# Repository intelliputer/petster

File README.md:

## The Petster Deluxe

An archival and reverse-engineering workspace for the Axlon Petster Deluxe electronic pet.

### What is preserved

Petster Deluxe is an electronic pet with a microprocessor-controlled behaviour system. It responds to sounds and touch, can be led by a leash, and uses forward sensing to avoid obstacles.

The central artifact is a 4 KiB ROM image. The 8039 is an Intel MCS-48-family controller with external program memory; the bundled 8048-family references and tools are included to support investigation of that ROM.

| Path | Purpose |
| --- | --- |
| [`code/petster.bin`](code/petster.bin) | Preserved 4,096-byte baseline ROM image. |
| [`code/petster.hex`](code/petster.hex) | Intel HEX encoding of the canonical ROM. |
| [`code/petster-array`](code/petster-array) | C-style byte-array representation. |
| [`code/PetsterDeluxeEprom.zip`](code/PetsterDeluxeEprom.zip) | Original-style archive containing the same ROM payload. |
| [`src/README.md`](src/README.md) | Read-only procedure for dumping the EPROM from the working Petster with the Barlino II. |
| [`src/petster_8039_linear.asm`](src/petster_8039_linear.asm) | Reproducible mechanical MCS-48/INS8039 assembly-style listing. |
| [`src/ROM-CONTROL-FLOW.md`](src/ROM-CONTROL-FLOW.md) | Tentative ROM control-flow map, with editable Mermaid source and SVG. |
| [`docs/`](docs) | Owner's manual, technical guide, and reference material. |
| [`docs/TECHNICAL-RESEARCH.md`](docs/TECHNICAL-RESEARCH.md) | Sourced 1985 hardware findings, preserved teardown, and open questions. |
| [`datasheets/`](datasheets) | INS8039-family reference datasheet. |
| [`docs/UNIT-OBSERVATIONS.md`](docs/UNIT-OBSERVATIONS.md) | Owner-reported markings and the evidence still needed from this specific cat. |
| [`tools/`](tools/README.md) | Period 8048/8039 development and analysis tools. |

### Hardware status

The 27C128 banked-ROM daughterboard is now a routed, two-layer PCB suitable
for a standard fabrication run. It adapts the Petster's 24-pin National
`NMC27C32` socket to a 28-pin `27C128`, with two jumpers selecting A12 and
A13 (four 4 KiB banks). Its functional pin assignments have been checked
against the NMC27C32B and 27C128 datasheets.

| Item | Current state |
| --- | --- |
| KiCad source | [`hardware/27c128-daughterboard/`](hardware/27c128-daughterboard/) |
| PCB | Routed, 45 × 45 mm, two copper layers, 0.20 mm tracks |
| Electrical rules check | 0 violations; 0 unconnected items in the prior KiCad check (2026-11-02); rerun before fabrication |
| Production archive | [`27c128-daughterboard.zip`](hardware/27c128-daughterboard/production/27c128-daughterboard.zip) |
| Latest fabrication export | Regenerated with KiCad 10.0.8 on 2026-11-03; J1 is now a 0.7 mm drilled 24-pin wide-DIP plug footprint |
| Solder mask | Present on both sides and on all plated pads |
| Hardware test | Pending continuity checks, then a controlled power-on test in the Petster |

This is a passive adapter: it relies on the Petster's existing +5 V supply
and external-ROM signals. Fit C1, both bank-select shunts, the 24-pin male
plug, and the 28-pin socket before use. Do not change bank jumpers while the
Petster is powered.

The companion 8039-II SBC is also released for fabrication. It is a two-layer
external-ROM MCS-48 bench computer with a socketed 8039, 74LS373 address latch,
27C32/27C128/27C256 ROM socket, FTDI Friend console, and a 20-pin expansion
header. Its 8039 multiplexed DB0-DB7 bus is connected to both the latch and
ROM; J2 instead exposes the spare P1/P2 GPIO and external-bus control signals.

| Item | Current state |
| --- | --- |
| KiCad source | [`hardware/8039-II-SBC/`](hardware/8039-II-SBC/) |
| PCB | Routed two-layer through-hole board; 0 unconnected pads |
| Design checks | ERC: 0 errors / 0 warnings; DRC: 0 violations (2026-11-05) |
| Production archive | [`8039-II-SBC.zip`](hardware/8039-II-SBC/production/8039-II-SBC.zip) |
| Electrical design | [`ELECTRICAL-ANALYSIS.md`](hardware/8039-II-SBC/ELECTRICAL-ANALYSIS.md) |
| Assembly status | Fabrication-ready; first assembled-board bring-up remains pending |

Use the [8039-II bring-up checklist](hardware/8039-II-SBC/BRING-UP.md) for
first power-up. Verify jumper positions and component orientation, then use a
current-limited 5 V source and a known-good diagnostic EPROM image.

### ROM integrity and physical provenance

The ZIP payload, Intel HEX file, `src` binary, and C-style byte array resolve
byte-for-byte to the preserved baseline image. The image is 4,096 bytes and
has this SHA-256 digest:

```text
609d6505297a6365abb4fdbd869a2d76aad65ebd2accc628e37023a11ffefee9
```

Run the following from the repository root to verify those representations:

```sh
./scripts/verify-rom.sh
```

The check requires standard POSIX utilities plus `unzip`, GNU `objcopy`, and `sha256sum`.

This proves that the repository copies agree; it does **not** prove the image
matches the ROM in any particular Petster Deluxe. The working Petster's EPROM
is the authority for that unit. Use the read-only
[`src/README.md`](src/README.md) procedure to make two independent Barlino II
reads, compare those reads with each other, then compare their hashes with the
baseline. Preserve a matching but different image as a separately documented
ROM revision.

See [`docs/TECHNICAL-RESEARCH.md`](docs/TECHNICAL-RESEARCH.md) before working on hardware. It records the 1985 external-ROM architecture, the ROM's verified used range, and the checks needed before attaching an adapter.

### Reverse-engineering status

This project does not yet contain a validated disassembly. Earlier generated listings were removed because one decoded the ROM as Motorola 68HC11 instructions and another as x86; neither is valid for an MCS-48-family target. A reproducible, mechanical MCS-48/8039 linear listing is available at [`src/petster_8039_linear.asm`](src/petster_8039_linear.asm). It preserves every ROM byte and calculates MCS-48 branch targets, but it deliberately does not claim code-versus-data classification, labels, or behavioural analysis.

The tentative map is available as [documentation](src/ROM-CONTROL-FLOW.md),
[editable Mermaid source](src/rom-control-flow.mmd), and a rendered
[SVG](src/rom-control-flow.svg). Update the Mermaid source before regenerating
the SVG as analysis improves.

Regenerate the listing with:

```sh
python3 scripts/disassemble-mcs48.py \
  'code/petster.bin' \
  src/petster_8039_linear.asm
```

#### How the listing was produced

1. The target was selected as the Intel MCS-48/INS8039 family from the
   external-ROM hardware evidence, rather than decoding the bytes as an
   unrelated CPU architecture.
2. [`scripts/disassemble-mcs48.py`](scripts/disassemble-mcs48.py) performs a
   deterministic linear sweep of the 4 KiB image. Its opcode definitions were
   cross-checked against the bundled historical 8048 disassembler source in
   [`tools/8048/8048dis.zip`](tools/8048/8048dis.zip).
3. The script decodes documented instruction forms, calculates `JMP` and
   `CALL` targets from their MCS-48 page fields, and calculates conditional
   branch targets within their current 256-byte page. Undefined opcodes are
   retained as `DB` directives. Long runs of erased `FF` bytes are likewise
   retained as `DB` directives rather than treated as executable code.
4. Every listing line includes its original address and bytes in a comment.
   The generated listing was parsed back into 4,096 bytes and compared
   byte-for-byte with the input image.

This method establishes a reproducible instruction-level view of the bytes;
it does not determine whether a decoded sequence is reachable code, embedded
data, a jump table, or an interrupt vector. Those classifications need
control-flow analysis plus observations from the physical Petster.

Treat `petster.bin` as the source of truth. A future disassembly should identify the exact MCS-48 tool and version, command line, ROM base address, CPU variant, and the byte ranges classified as code versus data. Contributions that add labels, hardware mappings, or behavioural analysis should cite the supporting manual, board observation, or ROM addresses.

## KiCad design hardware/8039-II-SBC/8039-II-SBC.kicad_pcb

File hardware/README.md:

# Petster 27C128 daughterboard

This is the active KiCad project for a passive, bank-selected adapter from
the Petster's 24-pin National `NMC27C32` socket to a 28-pin `27C128` EPROM.
It is for the external-ROM Petster revision.

The PCB is routed and has passed KiCad DRC with zero violations and zero
unconnected items. The manufacturing output is
[`production/27c128-daughterboard.zip`](production/27c128-daughterboard.zip).

## Function

`J1` is a 24-pin male-DIP plug on the underside. `U1` is the 28-pin EPROM
socket on top. The original address, data, enable, power, and ground signals
route directly between their equivalent pins. `JP1` selects A12 and `JP2`
selects A13, giving four 4 KiB banks. Change shunts only while the Petster is
unpowered.

### How a 24-pin socket accesses a 27C128

The Petster was designed for a 27C32: a 4 KiB × 8 EPROM with twelve address
inputs, `A0`–`A11`. The 8039 therefore always fetches from one 4 KiB program
window. Its multiplexed low address/data bus is latched externally, the upper
four address bits supply `A8`–`A11`, and `/CE` and `/OE` enable each EPROM
read.

The 27C128 is electrically compatible at the data and control interface, but
has 16 KiB of storage and therefore needs two more address inputs, `A12` and
`A13`. The board passes the original socket's `A0`–`A11`, `D0`–`D7`, `/CE`,
`/OE`, `+5 V`, and ground straight to their 27C128 equivalents. It adds no
logic, buffering, or address decoder.

The extra inputs are held at a defined logic level by the two three-pin
jumpers. Each jumper connects its address input to either ground (0) or +5 V
(1). The processor remains unaware of this selection: it still requests local
addresses `0x000`–`0xFFF`, but the jumper levels choose which physical 4 KiB
region in the 27C128 supplies the bytes. For example, with `A13:A12 = 10`, a
fetch from the processor's `0x000` is read from physical 27C128 address
`0x2000`.

| JP2 / A13 | JP1 / A12 | Exposed 27C128 address range | Bank |
| ---: | ---: | --- | ---: |
| 0 | 0 | `0x0000–0x0FFF` | 0 |
| 0 | 1 | `0x1000–0x1FFF` | 1 |
| 1 | 0 | `0x2000–0x2FFF` | 2 |
| 1 | 1 | `0x3000–0x3FFF` | 3 |

`VPP` and `/PGM` are tied to the voltage required by the fitted EPROM's normal
read mode; check the exact 27C128 manufacturer's datasheet before fitting.
C1 is a 100 nF ceramic bypass capacitor across the EPROM supply pins. Install
one shunt on each jumper: a floating address input makes bank selection
undefined. Never move a shunt while the Petster is powered; change banks with
power removed, or while the MCU is positively held in reset.

The complete functional pin map and bank truth table are in
[`SCHEMATIC-REVIEW.md`](SCHEMATIC-REVIEW.md). The release and assembly checks
are in [`PRODUCTION-READINESS.md`](PRODUCTION-READINESS.md).

## Assembly

Fit the 24-pin male plug, a 0.600-inch-wide 28-pin socket, both three-pin
headers and shunts, and C1 (100 nF ceramic). The PCB has no voltage regulator:
it uses the Petster's existing +5 V supply.

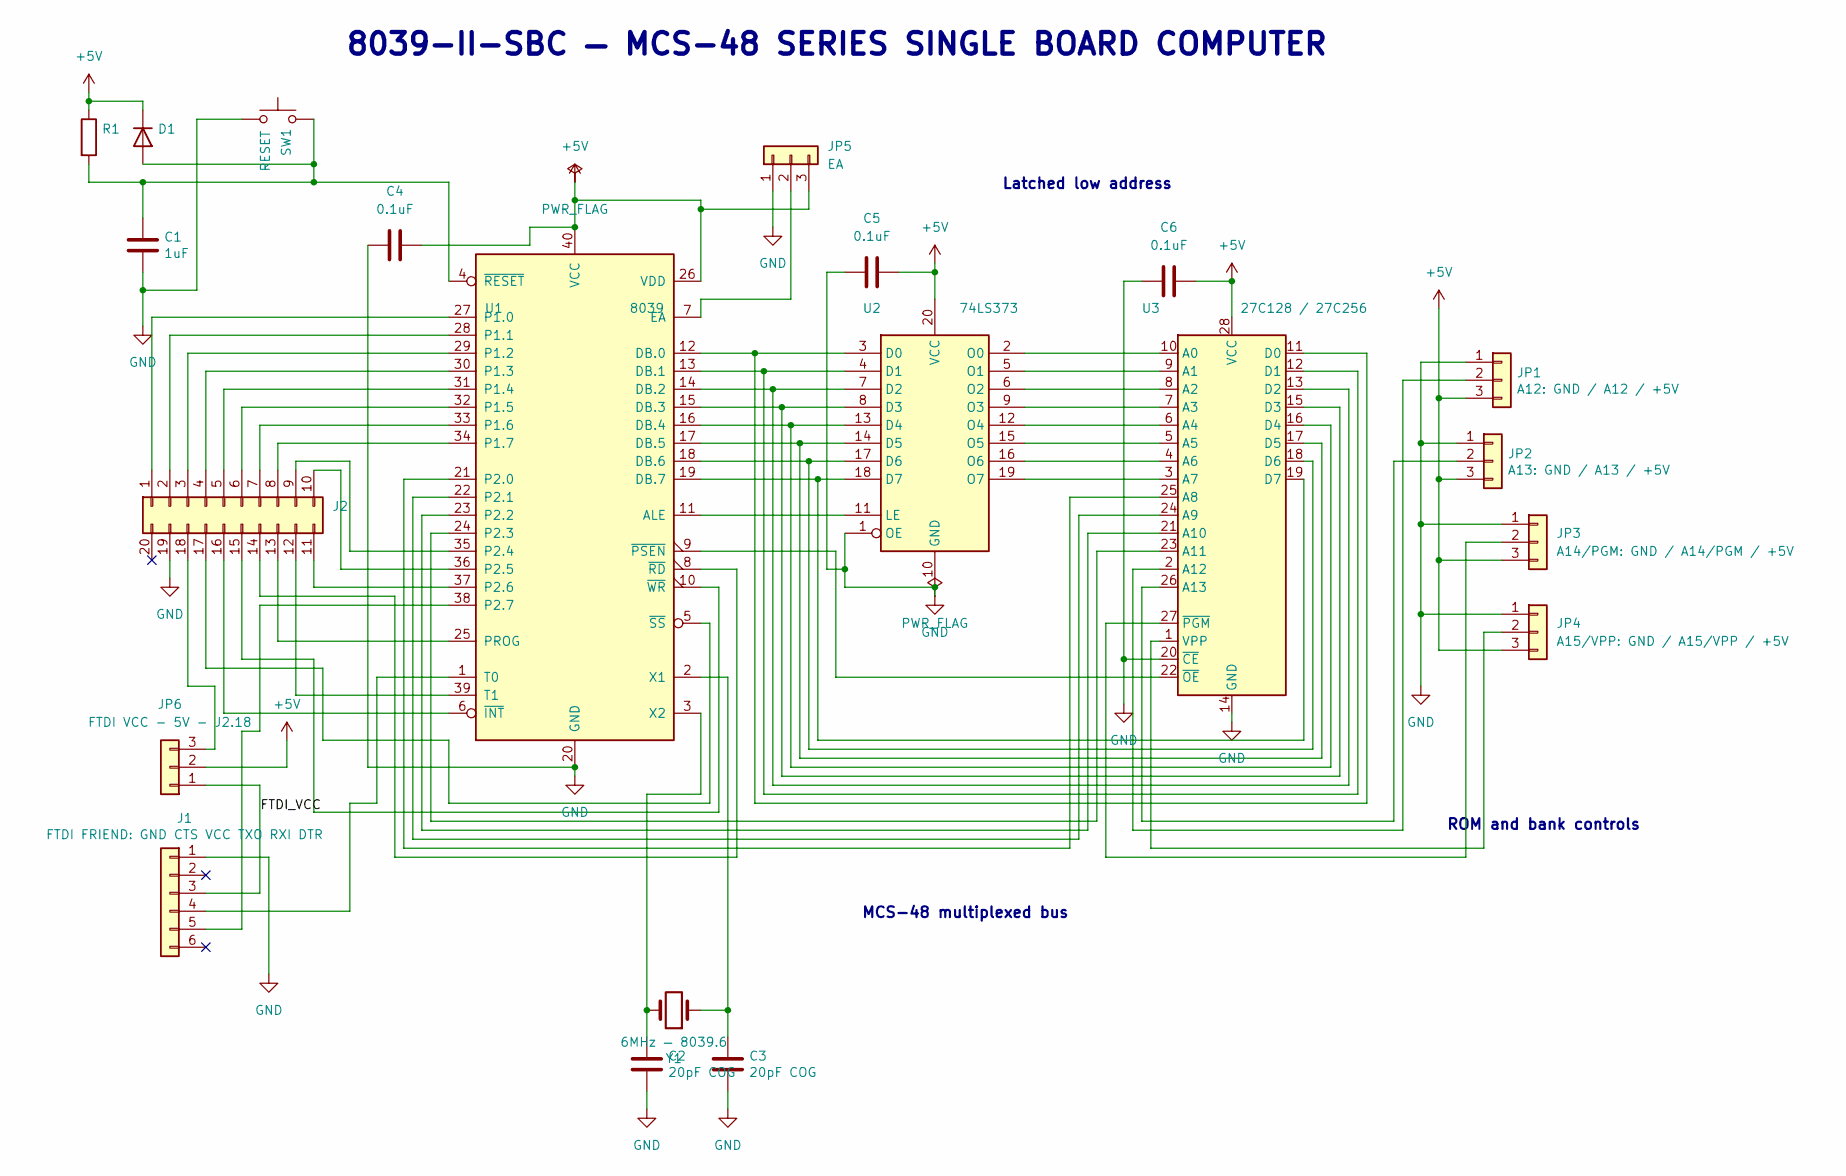
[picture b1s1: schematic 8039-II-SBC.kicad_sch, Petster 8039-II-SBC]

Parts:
C1: 1uF; CP_Radial_D5.0mm_P2.50mm
C2, C3: 20pF COG; C_Disc_D5.0mm_W2.5mm_P2.50mm
C4, C5, C6: 0.1uF; C_Disc_D5.0mm_W2.5mm_P2.50mm
D1: 1N4148 reset discharge; D_DO-35_SOD27_P10.16mm_Horizontal
J1: FTDI FRIEND: GND CTS VCC TXO RXI DTR; PinHeader_1x06_P2.54mm_Vertical
J2: Conn_02x10_Counter_Clockwise; PinHeader_2x10_P2.54mm_Vertical
JP1: A12: GND / A12 / +5V; PinHeader_1x03_P2.54mm_Vertical
JP2: A13: GND / A13 / +5V; PinHeader_1x03_P2.54mm_Vertical
JP3: A14/PGM: GND / A14/PGM / +5V; PinHeader_1x03_P2.54mm_Vertical
JP4: A15/VPP: GND / A15/VPP / +5V; PinHeader_1x03_P2.54mm_Vertical
JP5: EA; PinHeader_1x03_P2.54mm_Vertical
JP6: FTDI VCC - 5V - J2.18; PinHeader_1x03_P2.54mm_Vertical
R1: 100k RESET pull-up; R_Axial_DIN0207_L6.3mm_D2.5mm_P10.16mm_Horizontal
SW1: RESET; SW_PUSH_6mm_H5mm
U1: 8039; DIP-40_W15.24mm_Socket
U2: 74LS373; DIP-20_W7.62mm_Socket
U3: 27C128 / 27C256; DIP-28_W15.24mm_Socket
Y1: 6MHz — 8039.6; Crystal_HC49-U_Vertical

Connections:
+5V: C4.2, C5.2, C6.2, D1.1 (K), JP1.3, JP2.3, JP3.3, JP4.3, JP5.3, JP6.2, R1.1, U1.26 (VDD), U1.40 (VCC), U2.20 (VCC), U3.28 (VCC)
/FTDI_VCC: J1.3, JP6.1
GND: C1.2, C2.2, C3.2, C4.1, C5.1, C6.1, J1.1, J2.19, JP1.1, JP2.1, JP3.1, JP4.1, JP5.1, SW1.1, U1.20 (GND), U2.1 (OE), U2.10 (GND), U3.14 (GND), U3.20 (~CE)
unnamed: C1.1, D1.2 (A), R1.2, SW1.2, U1.4 (~RESET)
unnamed: J1.4, U1.1 (T0)
unnamed: J1.5, U1.38 (P2.7)
unnamed: J2.1, U1.27 (P1.0)
unnamed: J2.2, U1.28 (P1.1)
unnamed: J2.3, U1.29 (P1.2)
unnamed: J2.4, U1.30 (P1.3)
unnamed: J2.5, U1.31 (P1.4)
unnamed: J2.6, U1.32 (P1.5)
unnamed: J2.7, U1.33 (P1.6)
unnamed: J2.8, U1.34 (P1.7)
unnamed: J2.9, U1.35 (P2.4)
unnamed: J2.10, U1.36 (P2.5)
unnamed: J2.11, U1.37 (P2.6)
unnamed: J2.12, U1.39 (T1)
unnamed: J2.13, U1.25 (PROG)
unnamed: J2.14, U1.8 (~RD)
unnamed: J2.15, U1.10 (~WR)
unnamed: J2.16, U1.6 (~INT)
unnamed: J2.17, U1.5 (~SS)
unnamed: J2.18, JP6.3
unnamed: JP1.2, U3.2 (A12)
unnamed: JP2.2, U3.26 (A13)
unnamed: JP3.2, U3.27 (~PGM)
unnamed: JP4.2, U3.1 (VPP)
unnamed: JP5.2, U1.7 (EA)
unnamed: U1.11 (ALE), U2.11 (LE)
unnamed: U1.12 (DB.0), U2.3 (D0), U3.11 (D0)
unnamed: U1.13 (DB.1), U2.4 (D1), U3.12 (D1)
unnamed: U1.14 (DB.2), U2.7 (D2), U3.13 (D2)
unnamed: U1.15 (DB.3), U2.8 (D3), U3.15 (D3)
unnamed: U1.16 (DB.4), U2.13 (D4), U3.16 (D4)
unnamed: U1.17 (DB.5), U2.14 (D5), U3.17 (D5)
unnamed: U1.18 (DB.6), U2.17 (D6), U3.18 (D6)
unnamed: U1.19 (DB.7), U2.18 (D7), U3.19 (D7)
unnamed: U1.21 (P2.0), U3.25 (A8)
unnamed: U1.22 (P2.1), U3.24 (A9)
unnamed: U1.23 (P2.2), U3.21 (A10)
unnamed: U1.24 (P2.3), U3.23 (A11)
unnamed: C3.1, U1.2 (X1), Y1.1
unnamed: C2.1, U1.3 (X2), Y1.2
unnamed: U1.9 (~PSEN), U3.22 (~OE)
unnamed: U2.2 (O0), U3.10 (A0)
unnamed: U2.5 (O1), U3.9 (A1)
unnamed: U2.6 (O2), U3.8 (A2)
unnamed: U2.9 (O3), U3.7 (A3)
unnamed: U2.12 (O4), U3.6 (A4)
unnamed: U2.15 (O5), U3.5 (A5)
unnamed: U2.16 (O6), U3.4 (A6)
unnamed: U2.19 (O7), U3.3 (A7)

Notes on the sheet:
ROM and bank controls
Latched low address
MCS-48 multiplexed bus
8039-II-SBC — MCS-48 SERIES SINGLE BOARD COMPUTER

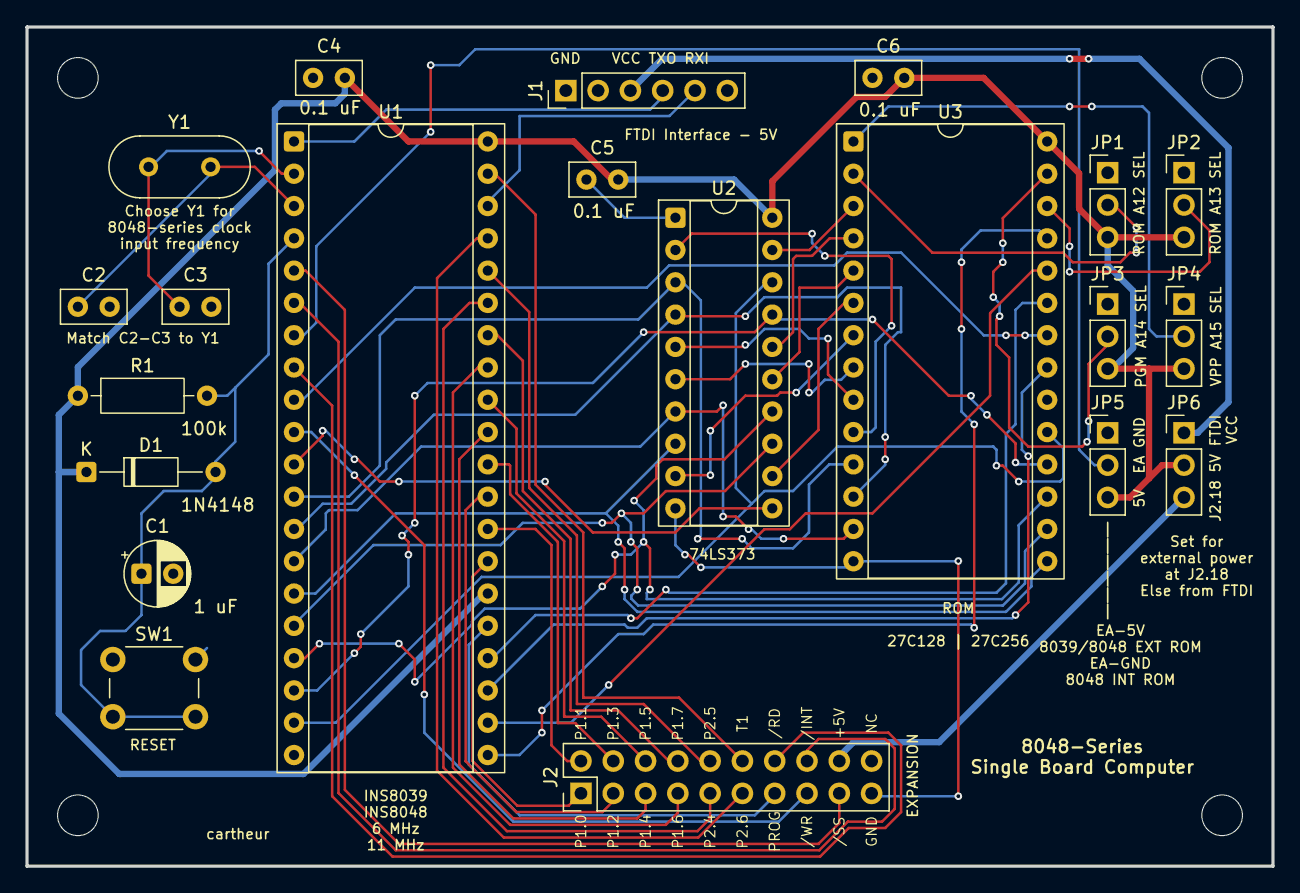
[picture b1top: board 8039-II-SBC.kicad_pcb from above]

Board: 2 copper layers, 98.0 x 66.0 mm, 25 parts (0 on the bottom side), 53 nets.

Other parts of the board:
H1, H2, H3, H4: MountingHole_3.2mm_M3

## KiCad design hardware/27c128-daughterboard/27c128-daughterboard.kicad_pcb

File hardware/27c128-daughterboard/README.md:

# Petster 27C128 daughterboard

This is the active KiCad project for a passive, bank-selected adapter from
the Petster's 24-pin National `NMC27C32` socket to a 28-pin `27C128` EPROM.
It is for the external-ROM Petster revision.

The PCB is routed and has passed KiCad DRC with zero violations and zero
unconnected items. The manufacturing output is
[`production/27c128-daughterboard.zip`](production/27c128-daughterboard.zip).

## Function

`J1` is a 24-pin male-DIP plug on the underside. `U1` is the 28-pin EPROM
socket on top. The original address, data, enable, power, and ground signals
route directly between their equivalent pins. `JP1` selects A12 and `JP2`
selects A13, giving four 4 KiB banks. Change shunts only while the Petster is
unpowered.

The complete functional pin map and bank truth table are in
[`SCHEMATIC-REVIEW.md`](SCHEMATIC-REVIEW.md). The release and assembly checks
are in [`PRODUCTION-READINESS.md`](PRODUCTION-READINESS.md).

## Assembly

Fit the 24-pin male plug, a 0.600-inch-wide 28-pin socket, both three-pin
headers and shunts, and C1 (100 nF ceramic). The PCB has no voltage regulator:
it uses the Petster's existing +5 V supply.

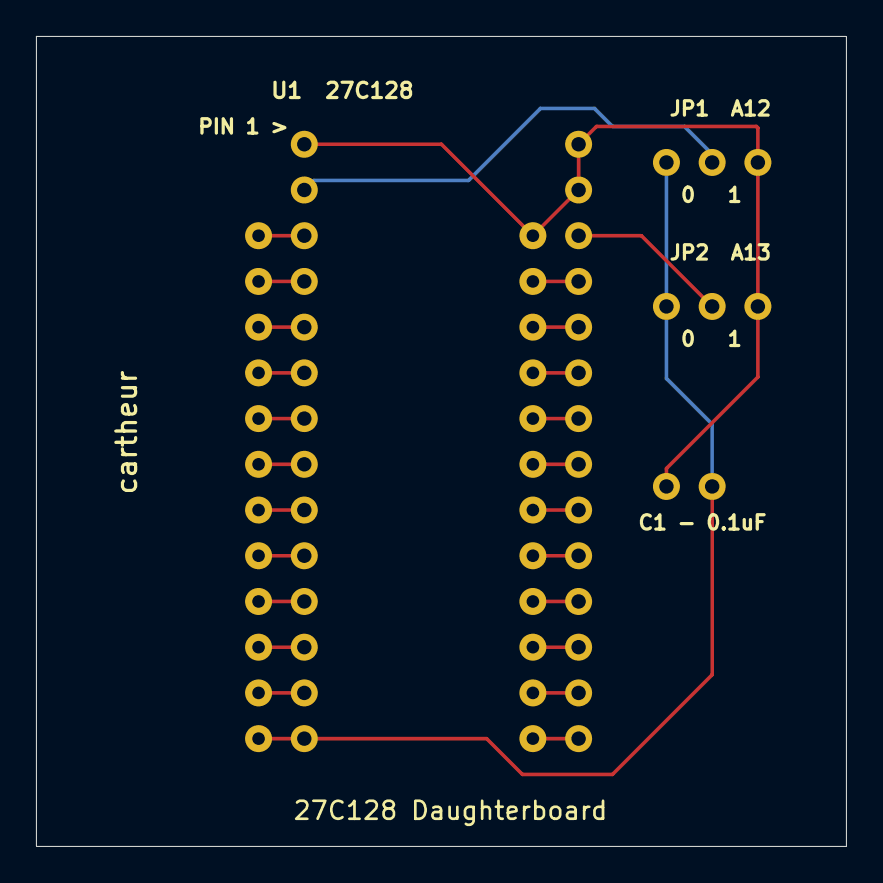
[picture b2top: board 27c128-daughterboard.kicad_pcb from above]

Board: 2 copper layers, 45.0 x 45.0 mm, 5 parts (0 on the bottom side), 26 nets.

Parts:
C1: 100nF ceramic, 2.54 mm lead spacing
J1: 24-pin male DIP plug to Petster NMC27C32 socket
JP1, JP2: BANK SELECT: 0-GND / 1-+5V
U1: 27C128 wide DIP-28 socket

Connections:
+5V: C1.1, J1.24, JP1.3, JP2.3, U1.1, U1.27, U1.28
A0: J1.8, U1.10
A1: J1.7, U1.9
A2: J1.6, U1.8
A3: J1.5, U1.7
A4: J1.4, U1.6
A5: J1.3, U1.5
A6: J1.2, U1.4
A7: J1.1, U1.3
A8: J1.23, U1.25
A9: J1.22, U1.24
A10: J1.19, U1.21
A11: J1.21, U1.23
A12_BANK: JP1.2, U1.2
A13_BANK: JP2.2, U1.26
D0: J1.9, U1.11
D1: J1.10, U1.12
D2: J1.11, U1.13
D3: J1.13, U1.15
D4: J1.14, U1.16
D5: J1.15, U1.17
D6: J1.16, U1.18
D7: J1.17, U1.19
GND: C1.2, J1.12, JP1.1, JP2.1, U1.14
~CE: J1.18, U1.20
~OE: J1.20, U1.22
